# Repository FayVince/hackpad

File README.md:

# Hackpad
I just wanted to make external arrows with a clean design. I added a volume controller and an esc key too.

# Shematic

# PCB

# The case

# BOM
  - 5 MX Cherry switch
  - EC11 Rotary encoder
  - 1x XIAO RP2040
  - 5x blank keycap (maybe I'll replace them with 3D printed ones later)
  - 4x M3 bolt
  - 4x M3 heatset

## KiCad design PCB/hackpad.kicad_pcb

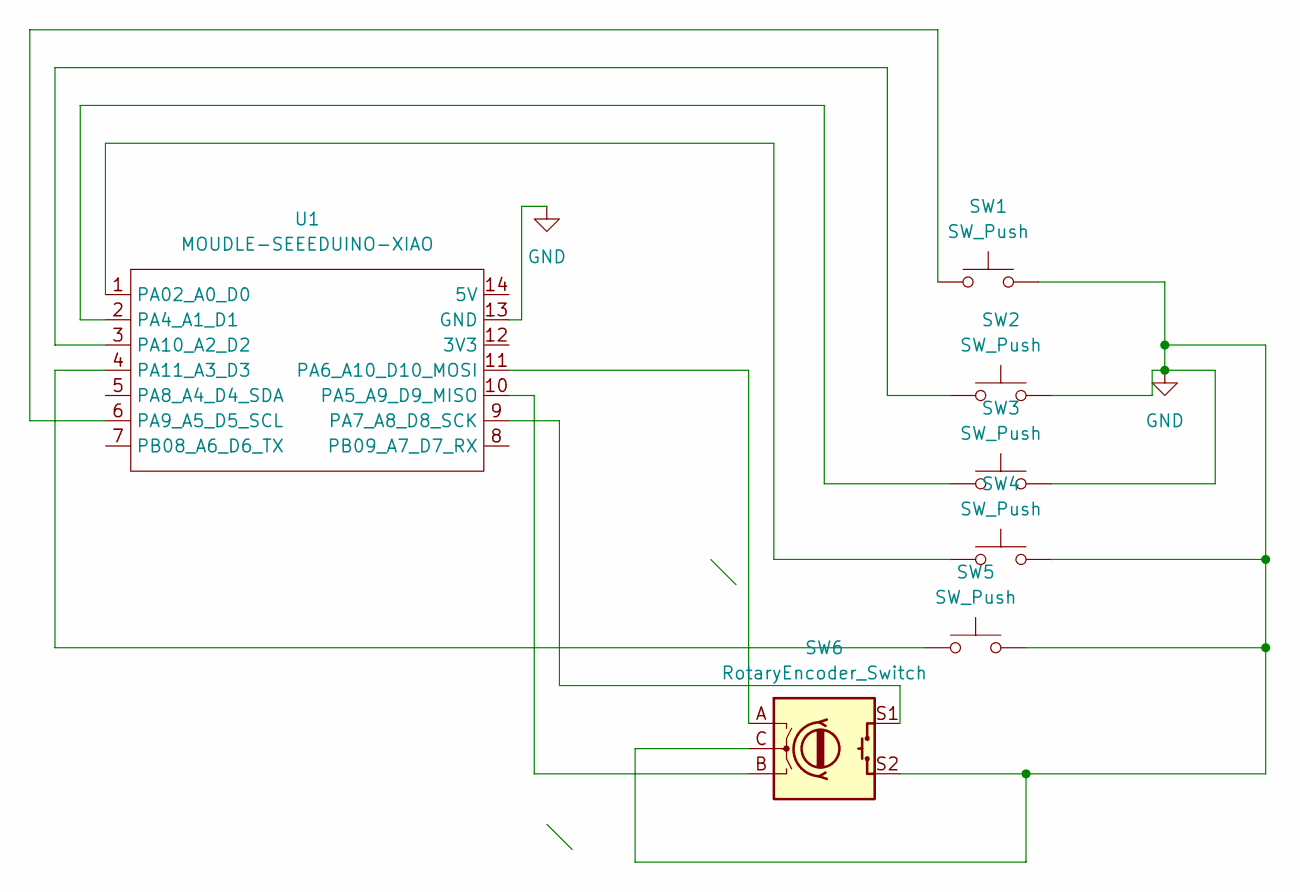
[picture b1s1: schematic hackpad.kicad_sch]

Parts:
SW1, SW2, SW3, SW4, SW5: SW_Push; SW_Cherry_MX_1.00u_PCB
SW6: RotaryEncoder_Switch; RotaryEncoder_Alps_EC11E-Switch_Vertical_H20mm
U1: MOUDLE-SEEEDUINO-XIAO; XIAO-Generic-Hybrid-14P-2.54-21X17.8MM

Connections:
GND: SW1.2, SW2.2, SW3.2, SW4.2, SW5.2, SW6.C, SW6.S2, U1.13 (GND)
unnamed: SW4.1, U1.1 (PA02_A0_D0)
unnamed: SW3.1, U1.2 (PA4_A1_D1)
unnamed: SW6.B, U1.10 (PA5_A9_D9_MISO)
unnamed: SW6.A, U1.11 (PA6_A10_D10_MOSI)
unnamed: SW6.S1, U1.9 (PA7_A8_D8_SCK)
unnamed: SW1.1, U1.6 (PA9_A5_D5_SCL)
unnamed: SW2.1, U1.3 (PA10_A2_D2)
unnamed: SW5.1, U1.4 (PA11_A3_D3)

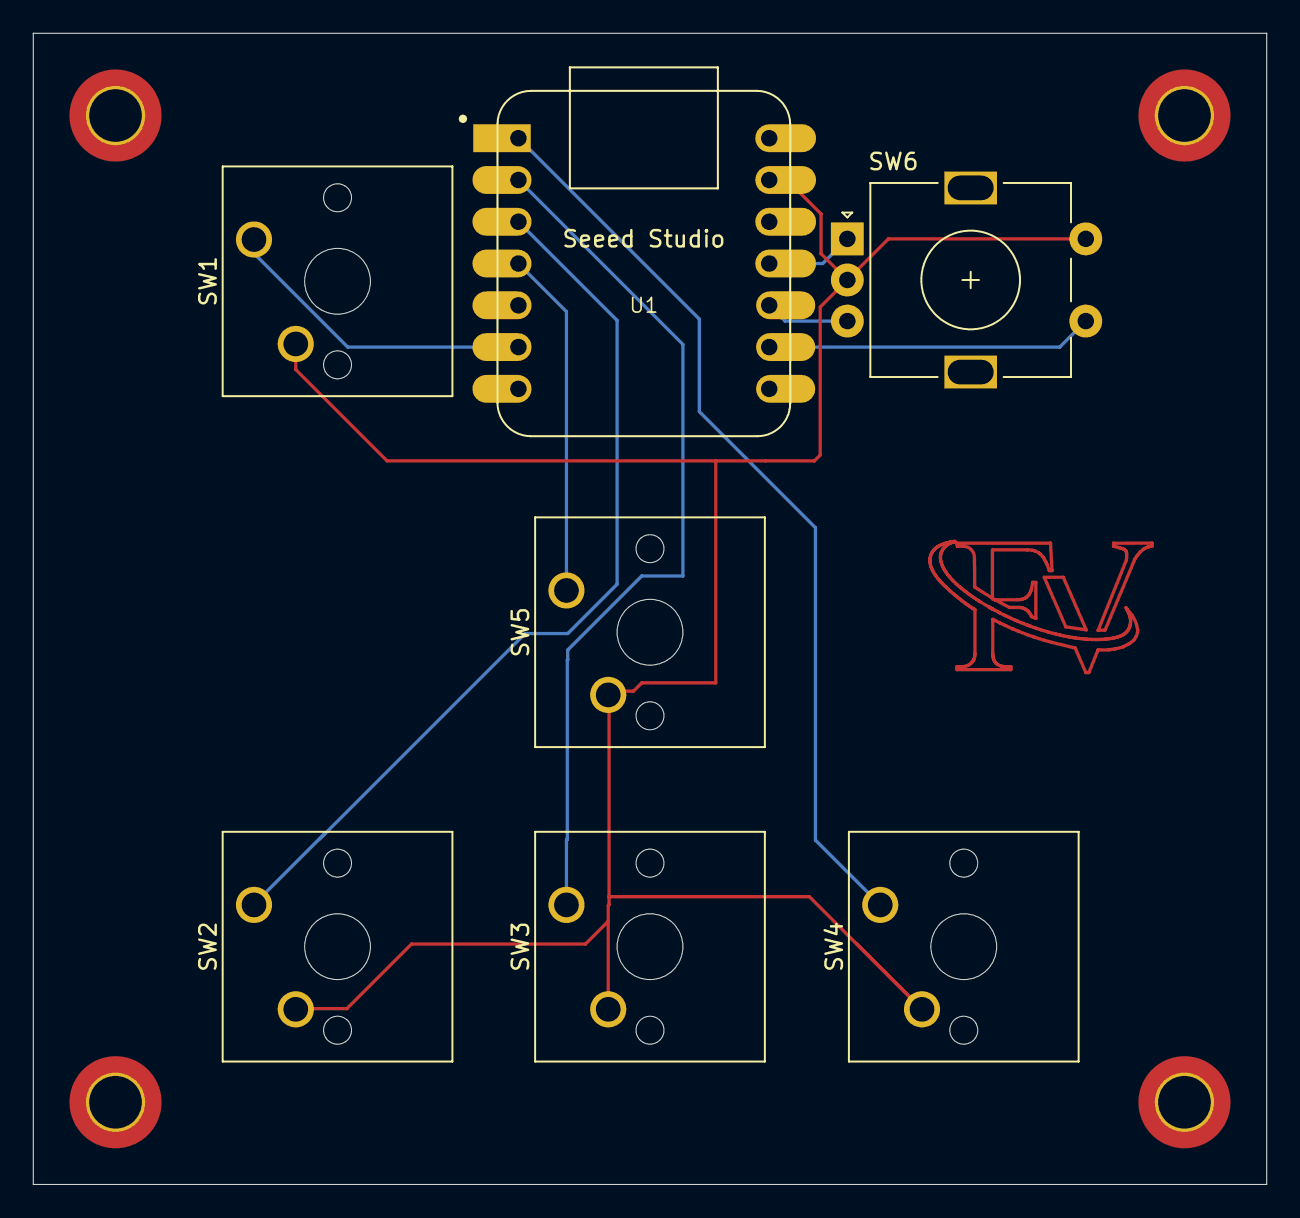
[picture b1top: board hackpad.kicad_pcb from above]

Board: 2 copper layers, 75.0 x 70.0 mm, 7 parts (0 on the bottom side), 9 nets.

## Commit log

2026-03-03 Create cad
2026-03-03 Create pcb
2026-03-03 Create prod
2026-03-03 Add KiCad project, move firmware, add release zip
    Add KiCad project files for the hackpad PCB (PCB/hackpad.kicad_pcb, .kicad_pro, .kicad_sch) including the full board layout. Remove legacy CAD artifacts (PCB/pcb, cad/cad) and remove production/prod.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
2026-03-03 Update README with project details and BOM
    Added detailed project description, schematic, PCB images, and BOM.
2026-03-03 Enhance README with design details and images
    Updated the README with a clearer description and added images for better visualization.
2026-03-03 Migrate keyboard firmware to KMK; remove QMK files
    Rename firmware.py -> firmware/firmware.py and add production/firmware.py implementing the device in KMK (GPIO pin assignments, keymap, rotary encoder handlers and press behavior). Remove legacy QMK 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
2026-04-16 Refactor firmware.py to use EncoderHandler and MediaKeys
